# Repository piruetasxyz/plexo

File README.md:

# plexo

Multiplexor de 6 potenciómetros para Raspberry Pi Pico.

Usa un 74HC4051 (multiplexor analógico de 8 canales) para leer 6 potenciómetros con una sola entrada analógica (ADC) de la Pico y 3 pines digitales de selección.

## Componentes

| Referencia | Valor | Encapsulado | Notas |
| --- | --- | --- | --- |
| U1 | 74HC4051 | SOIC-16 | LCSC C9386 |
| RV1–RV6 | 10k lineal (B10K) | 9 mm vertical, tipo Alpha RV09 | Se sueldan a mano |
| C1–C6 | 100 nF X7R | 0805 | Filtro en cada potenciómetro, LCSC C49678 |
| C7 | 100 nF X7R | 0805 | Desacople de U1, LCSC C49678 |
| J3 | Conector hembra 1×6 | 2,54 mm | Ver conexiones |

## Conexiones

J3 es un conector hembra de 6 pines, paso 2,54 mm.

| Pin | Señal | Pico (sugerido) |
| --- | --- | --- |
| 1 | 3V3 | 3V3(OUT), pin 36 |
| 2 | salida (COM del multiplexor) | GP26 / ADC0, pin 31 |
| 3 | GND | AGND, pin 33 |
| 4 | S0 | GP2, pin 4 |
| 5 | S1 | GP3, pin 5 |
| 6 | S2 | GP4, pin 6 |

Conviene conectar la tierra de plexo al pin AGND de la Pico (pin 33) en vez de una GND digital: las lecturas salen con menos ruido.

No alimentes los potenciómetros desde ADC_VREF. En la Pico ese pin tiene una resistencia de 200 Ω en serie, y los 6 potenciómetros consumen unos 2 mA en total, lo que hace caer el voltaje unos 0,4 V.

## Tabla de selección

| S2 | S1 | S0 | Canal | Lectura |
| --- | --- | --- | --- | --- |
| 0 | 0 | 0 | A0 | potenciómetro 1 |
| 0 | 0 | 1 | A1 | potenciómetro 2 |
| 0 | 1 | 0 | A2 | potenciómetro 3 |
| 0 | 1 | 1 | A3 | potenciómetro 4 |
| 1 | 0 | 0 | A4 | potenciómetro 5 |
| 1 | 0 | 1 | A5 | potenciómetro 6 |
| 1 | 1 | 0 | A6 | GND (lee 0) |
| 1 | 1 | 1 | A7 | GND (lee 0) |

Los canales A6 y A7 están conectados a tierra. Sirven para revisar cuánto mide el "cero" del ADC.

## Ejemplo en MicroPython

```python
from machine import ADC, Pin
import time

seleccion = [Pin(2, Pin.OUT), Pin(3, Pin.OUT), Pin(4, Pin.OUT)]  # S0, S1, S2
salida = ADC(26)

def leer_potenciometro(canal):
    for bit, pin in enumerate(seleccion):
        pin.value((canal >> bit) & 1)
    time.sleep_us(10)  # tiempo para que se estabilice el multiplexor
    salida.read_u16()  # se descarta la primera lectura
    return salida.read_u16()

while True:
    valores = [leer_potenciometro(canal) for canal in range(6)]
    print(valores)
    time.sleep_ms(50)
```

`read_u16()` entrega valores entre 0 y 65535.

## Notas

- Si el valor de un potenciómetro baja al girarlo en sentido horario, el potenciómetro tiene los pines al revés. Se puede invertir en el código con `65535 - valor`.
- Los potenciómetros genéricos de 9 mm (por ejemplo de AliExpress) varían un poco en la posición de las patas de montaje. Antes de mandar a fabricar, imprime el PCB a escala 1:1 y prueba que calce uno real.

## Archivos

- `plexo-v-0-rev-a/`: proyecto de KiCad (esquemático y PCB).

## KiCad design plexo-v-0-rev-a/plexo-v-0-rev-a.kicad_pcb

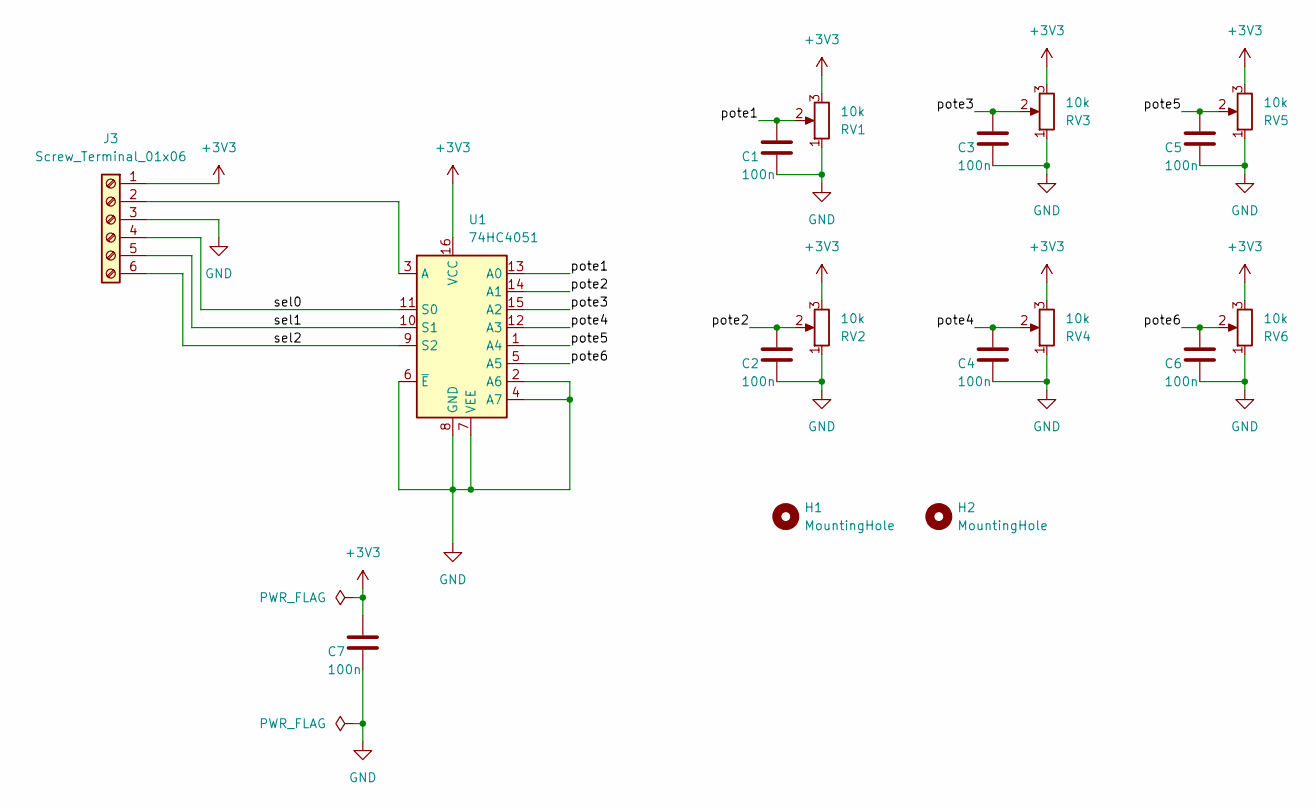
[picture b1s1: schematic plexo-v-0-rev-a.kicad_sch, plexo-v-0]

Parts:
C1, C2, C3, C4, C5, C6, C7: 100n; C_0805_2012Metric; LCSC C49678
H1, H2: MountingHole; MountingHole_3.2mm_M3
J3: Screw_Terminal_01x06; PinSocket_1x06_P2.54mm_Vertical
RV1, RV2, RV3, RV4, RV5, RV6: 10k; Potentiometer_Alpha_RD901F-40-00D_Single_Vertical
U1: 74HC4051; SOIC-16_3.9x9.9mm_P1.27mm; LCSC C9386

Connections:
+3V3: C7.1, J3.1, RV1.3, RV2.3, RV3.3, RV4.3, RV5.3, RV6.3, U1.16 (VCC)
/pote1: C1.1, RV1.2, U1.13 (A0)
/pote2: C2.1, RV2.2, U1.14 (A1)
/pote3: C3.1, RV3.2, U1.15 (A2)
/pote4: C4.1, RV4.2, U1.12 (A3)
/pote5: C5.1, RV5.2, U1.1 (A4)
/pote6: C6.1, RV6.2, U1.5 (A5)
/sel0: J3.4, U1.11 (S0)
/sel1: J3.5, U1.10 (S1)
/sel2: J3.6, U1.9 (S2)
GND: C1.2, C2.2, C3.2, C4.2, C5.2, C6.2, C7.2, J3.3, RV1.1, RV2.1, RV3.1, RV4.1, RV5.1, RV6.1, U1.2 (A6), U1.4 (A7), U1.6 (~E), U1.7 (VEE), U1.8 (GND)
unnamed: J3.2, U1.3 (A)

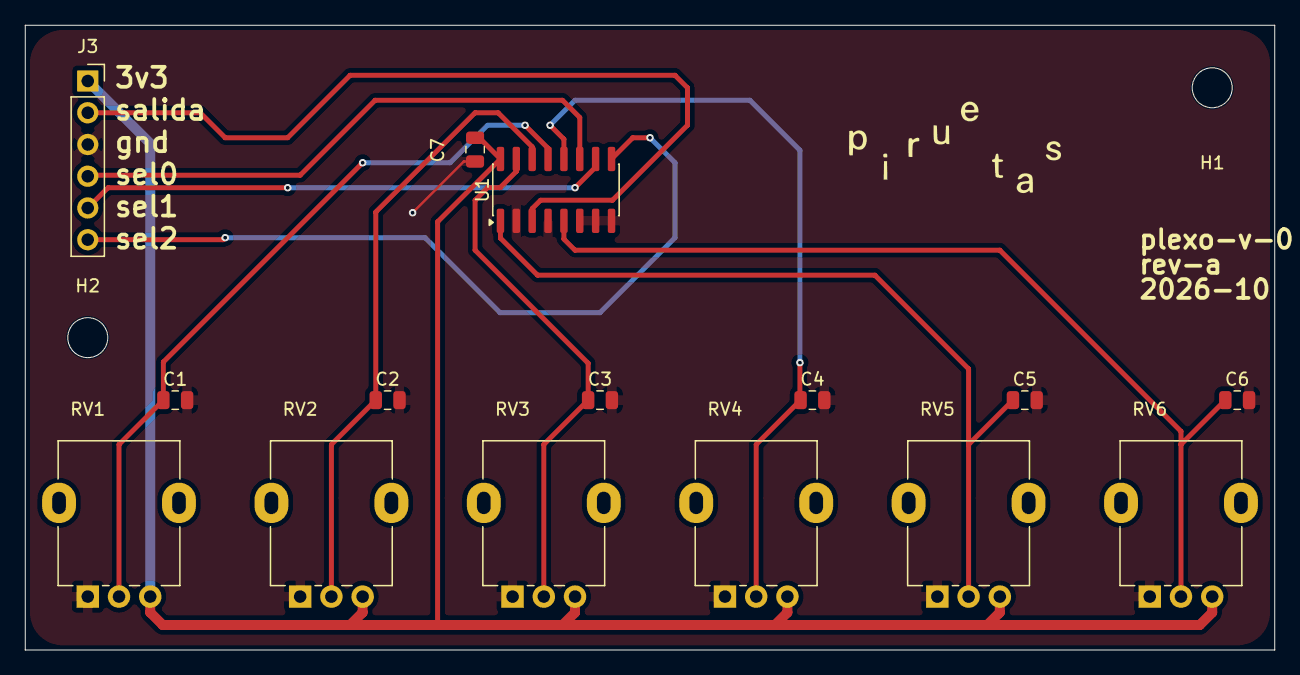
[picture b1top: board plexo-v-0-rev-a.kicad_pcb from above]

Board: 2 copper layers, 100.0 x 50.0 mm, 17 parts (0 on the bottom side), 12 nets.
